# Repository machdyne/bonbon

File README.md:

# Bonbon Computer

Bonbon is a compact FPGA computer designed by Lone Dynamics Corporation.

This repo contains schematics, PCB layouts, pinouts, example firmware, gateware and documentation.

Find more information on the [Bonbon product page](https://machdyne.com/product/bonbon-computer/).

## Blinky 

Building the blinky example requires [Yosys](https://github.com/YosysHQ/yosys), [nextpnr-ice40](https://github.com/YosysHQ/nextpnr) and [IceStorm](https://github.com/YosysHQ/icestorm).

Assuming they are installed, you can simply type `make` to build the gateware, which will be written to output/blinky.bin. You can then connect the Micro-USB port to your computer and use the latest version of [ldprog](https://github.com/machdyne/ldprog) to write the gateware to the device.

## Programming

The RP2040 firmware, FPGA SRAM and flash MMOD can be programmed over the Micro-USB port.

Configure the FPGA SRAM:

```
$ ldprog -b -s blinky.bin
```

Program the flash MMOD:

```
$ ldprog -b -f blinky.bin
```

Note: It should also be possible to program the MMOD over the USB-C port with a USB bootloader but this is not yet officially supported.

## Firmware

Bonbon ships with RP2040 [firmware](firmware) based on the [Müsli](https://github.com/machdyne/musli) firmware which allows it to communicate with [ldprog](https://github.com/machdyne/ldprog).

The firmware is responsible for initializing the system, [configuring and outputting the system clock](https://raspberrypi.github.io/pico-sdk-doxygen/group__hardware__clocks.html#details), and either configuring the FPGA or telling the FPGA to configure itself from the MMOD.

The system clock (CLK\_RP) is 48MHz by default.

The firmware can be updated by holding down the BOOTSEL button, connecting the Micro-USB port to your computer, and then dragging and dropping a new UF2 file to the device filesystem.

## DDMI

See this [SmolDVI fork](https://github.com/machdyne/SmolDVI) for an example of outputting video on the DDMI port.

## Pinouts

 * [MMOD](https://github.com/machdyne/mmod)
 * [DDMI](https://github.com/machdyne/ddmi)

## License

The contents of this repo are released under the [Lone Dynamics Open License](LICENSE.md) with the following exceptions:

- The KiCad design files contain parts of the [kicad-pmod](https://github.com/mithro/kicad-pmod) library which is released under the [Apache License, Version 2.0](https://www.apache.org/licenses/LICENSE-2.0.html).

- The KiCad design files may contain symbols and footprints released under other licenses; please contact us if we've failed to give proper attribution.

Note: You can use these designs for commercial purposes but we ask that instead of producing exact clones, that you either replace our trademarks and logos with your own or add your own next to ours.

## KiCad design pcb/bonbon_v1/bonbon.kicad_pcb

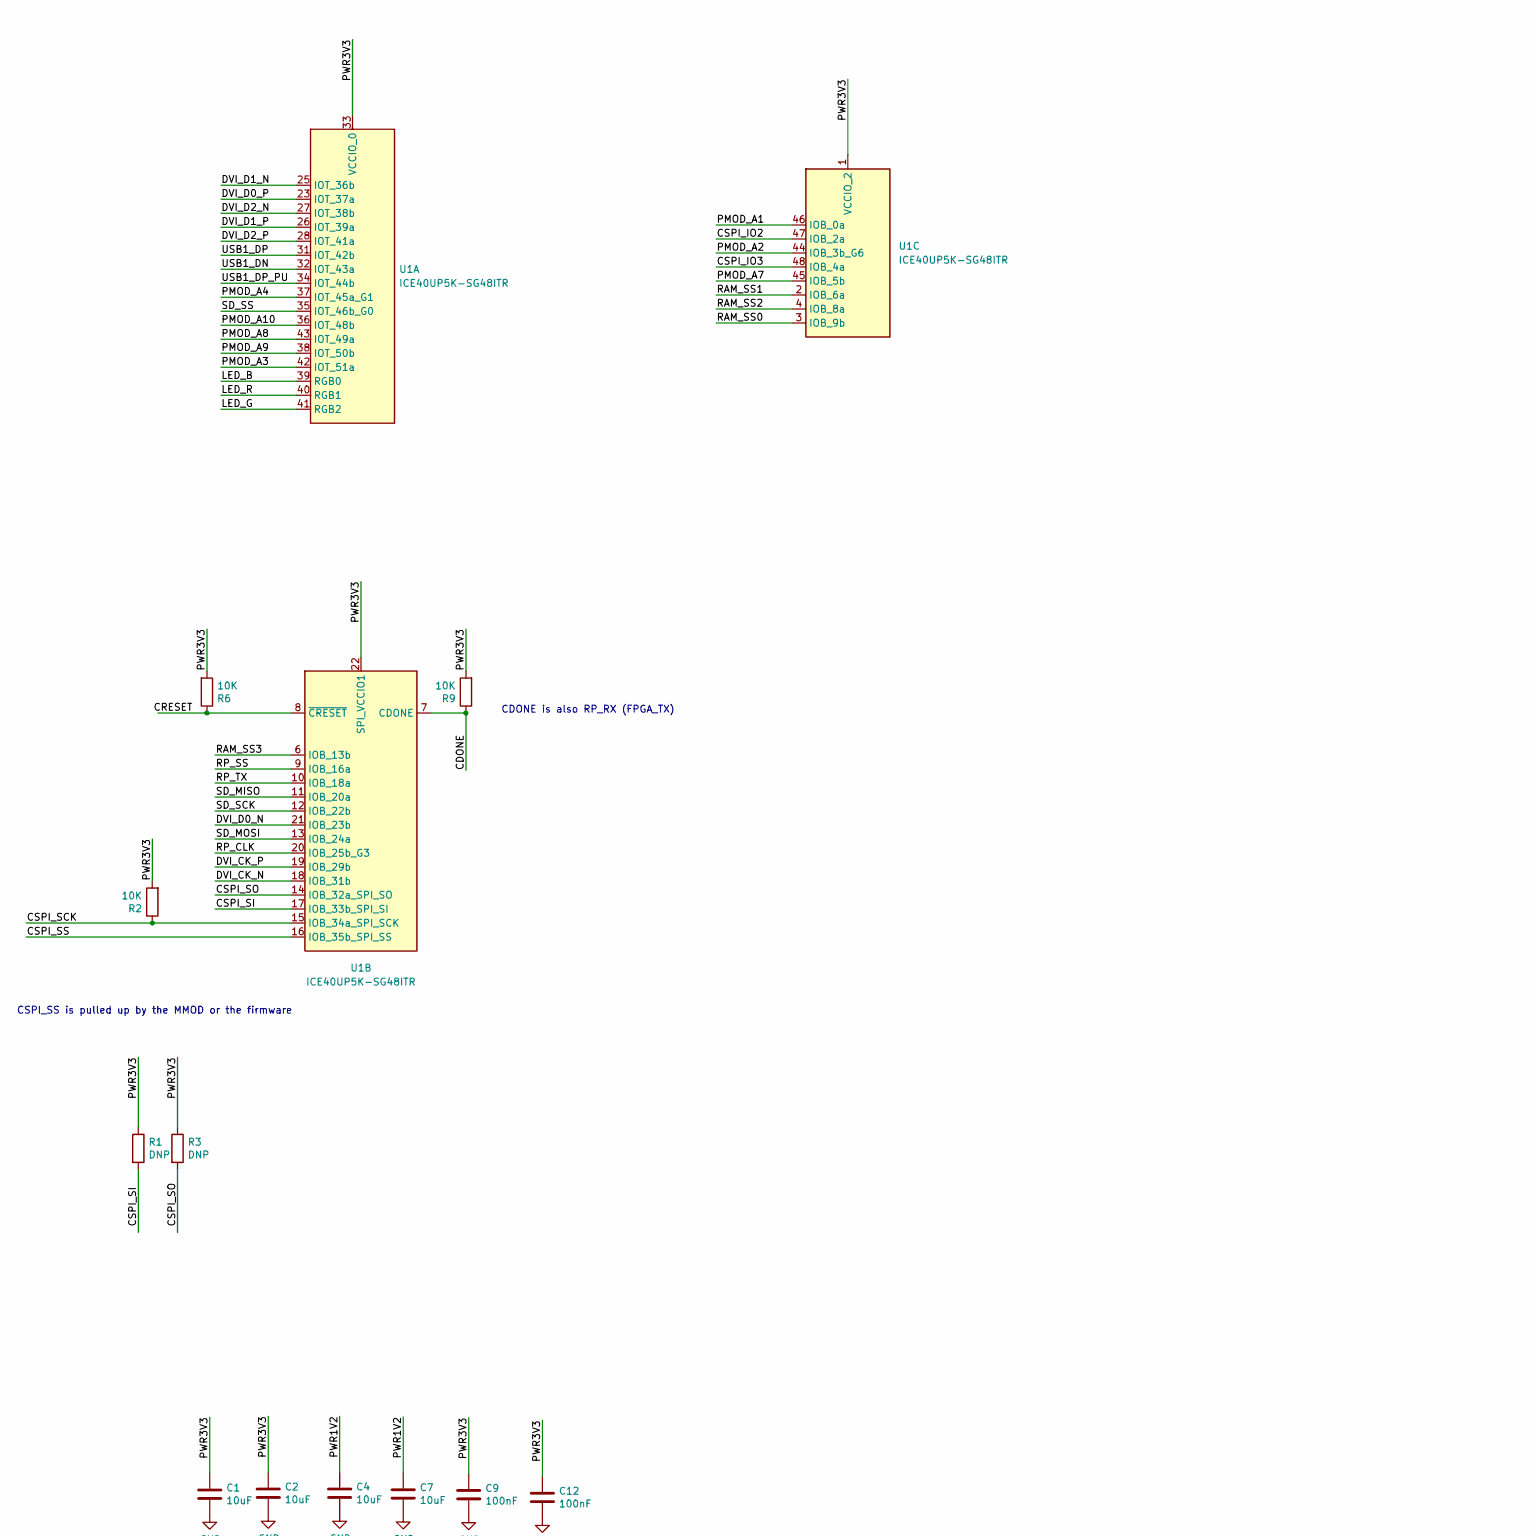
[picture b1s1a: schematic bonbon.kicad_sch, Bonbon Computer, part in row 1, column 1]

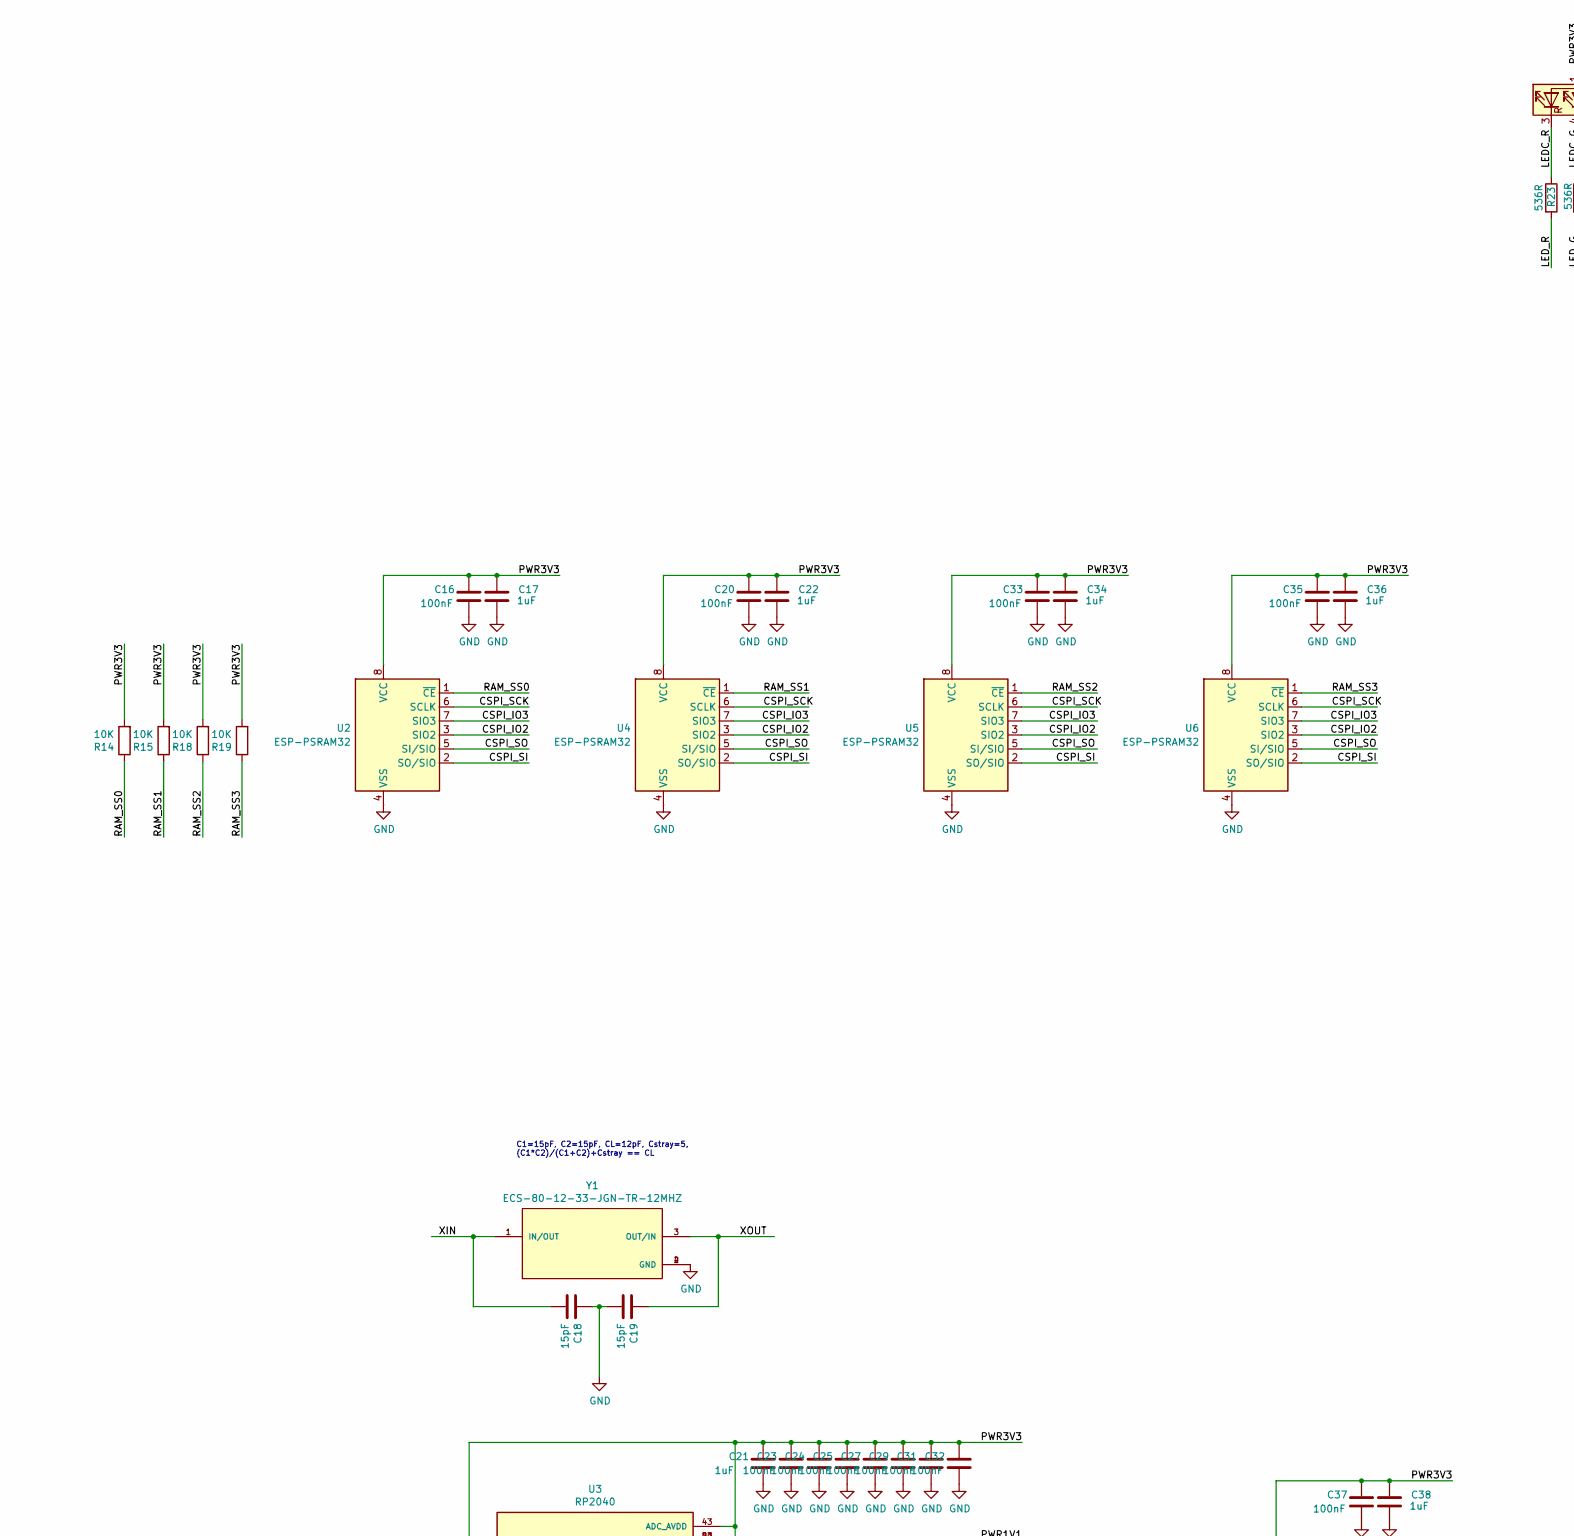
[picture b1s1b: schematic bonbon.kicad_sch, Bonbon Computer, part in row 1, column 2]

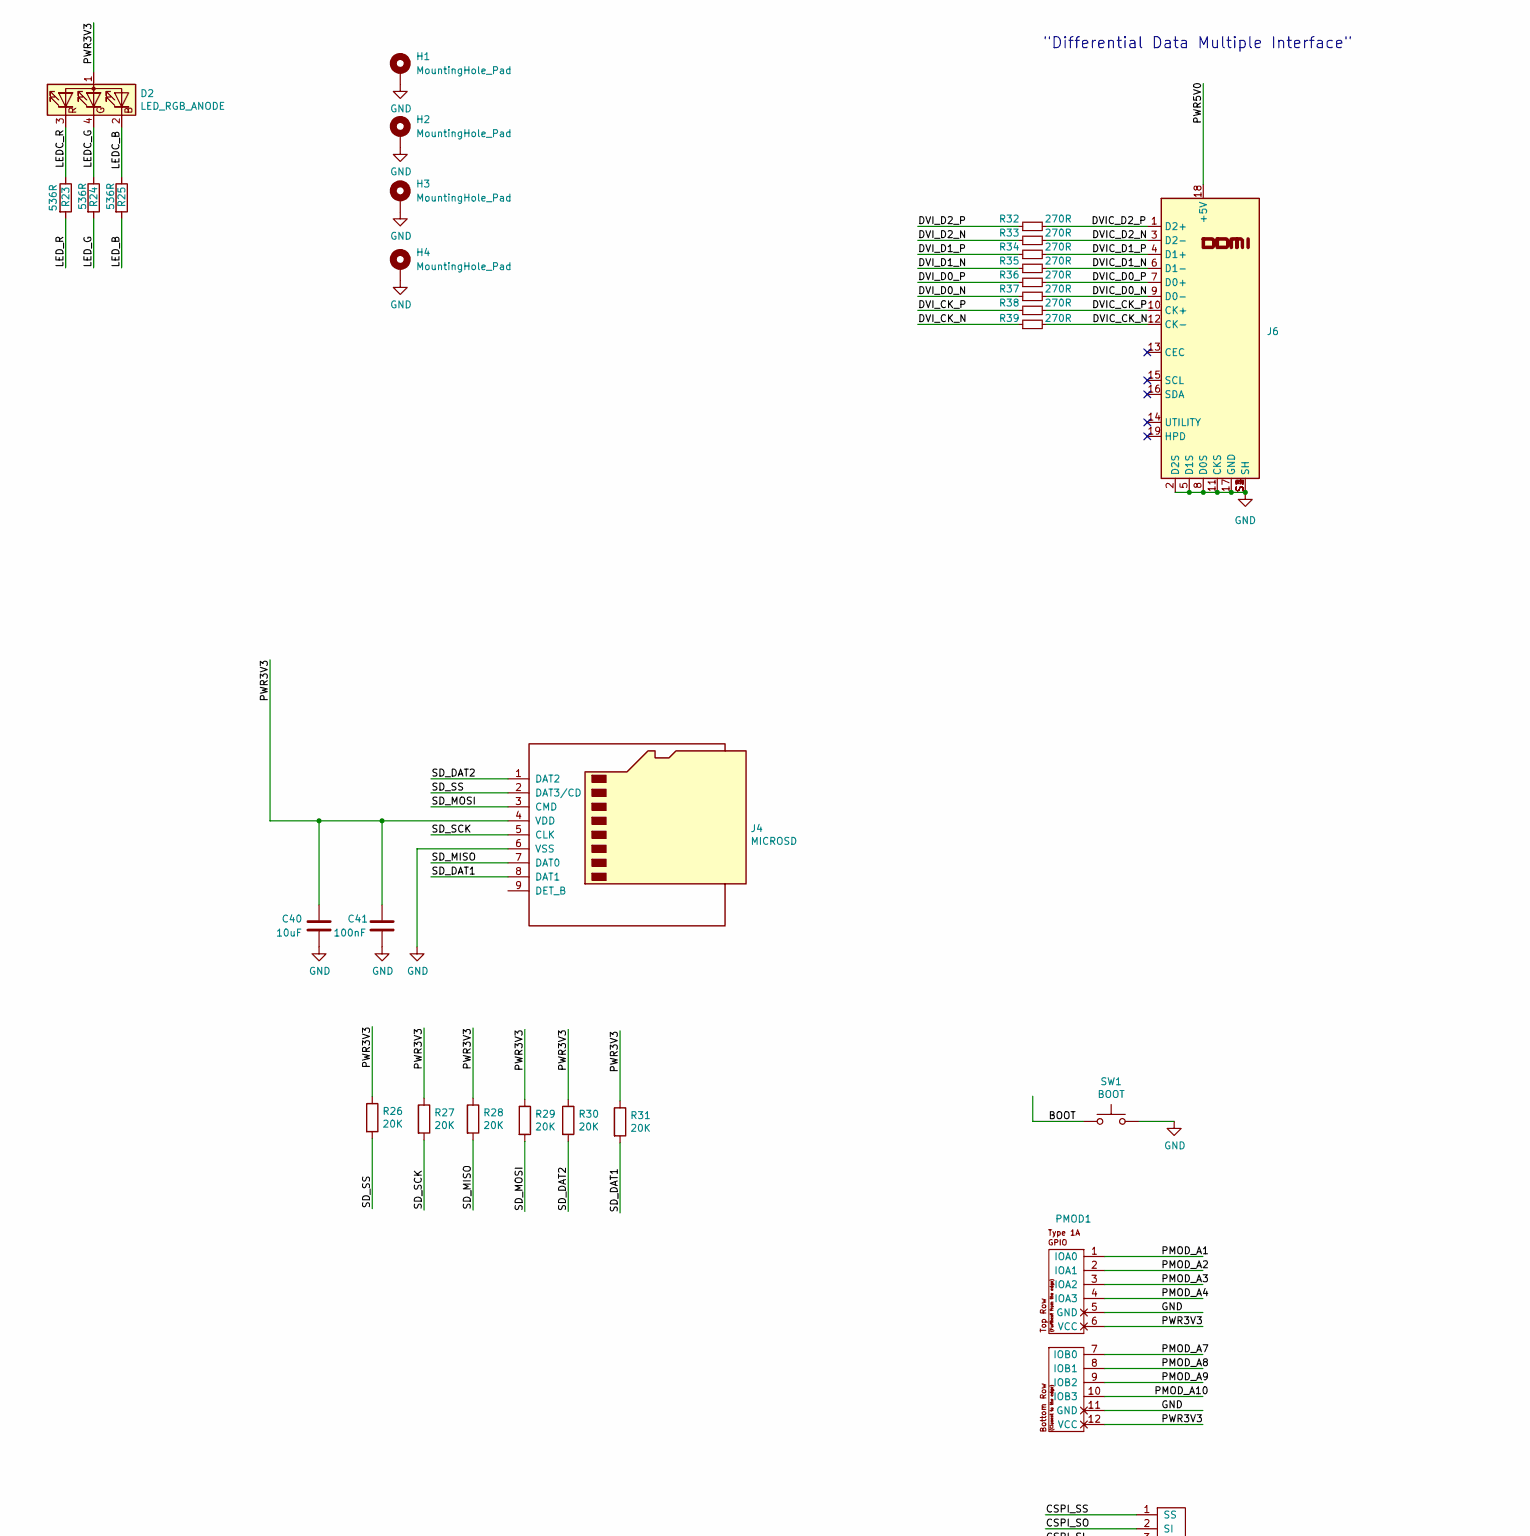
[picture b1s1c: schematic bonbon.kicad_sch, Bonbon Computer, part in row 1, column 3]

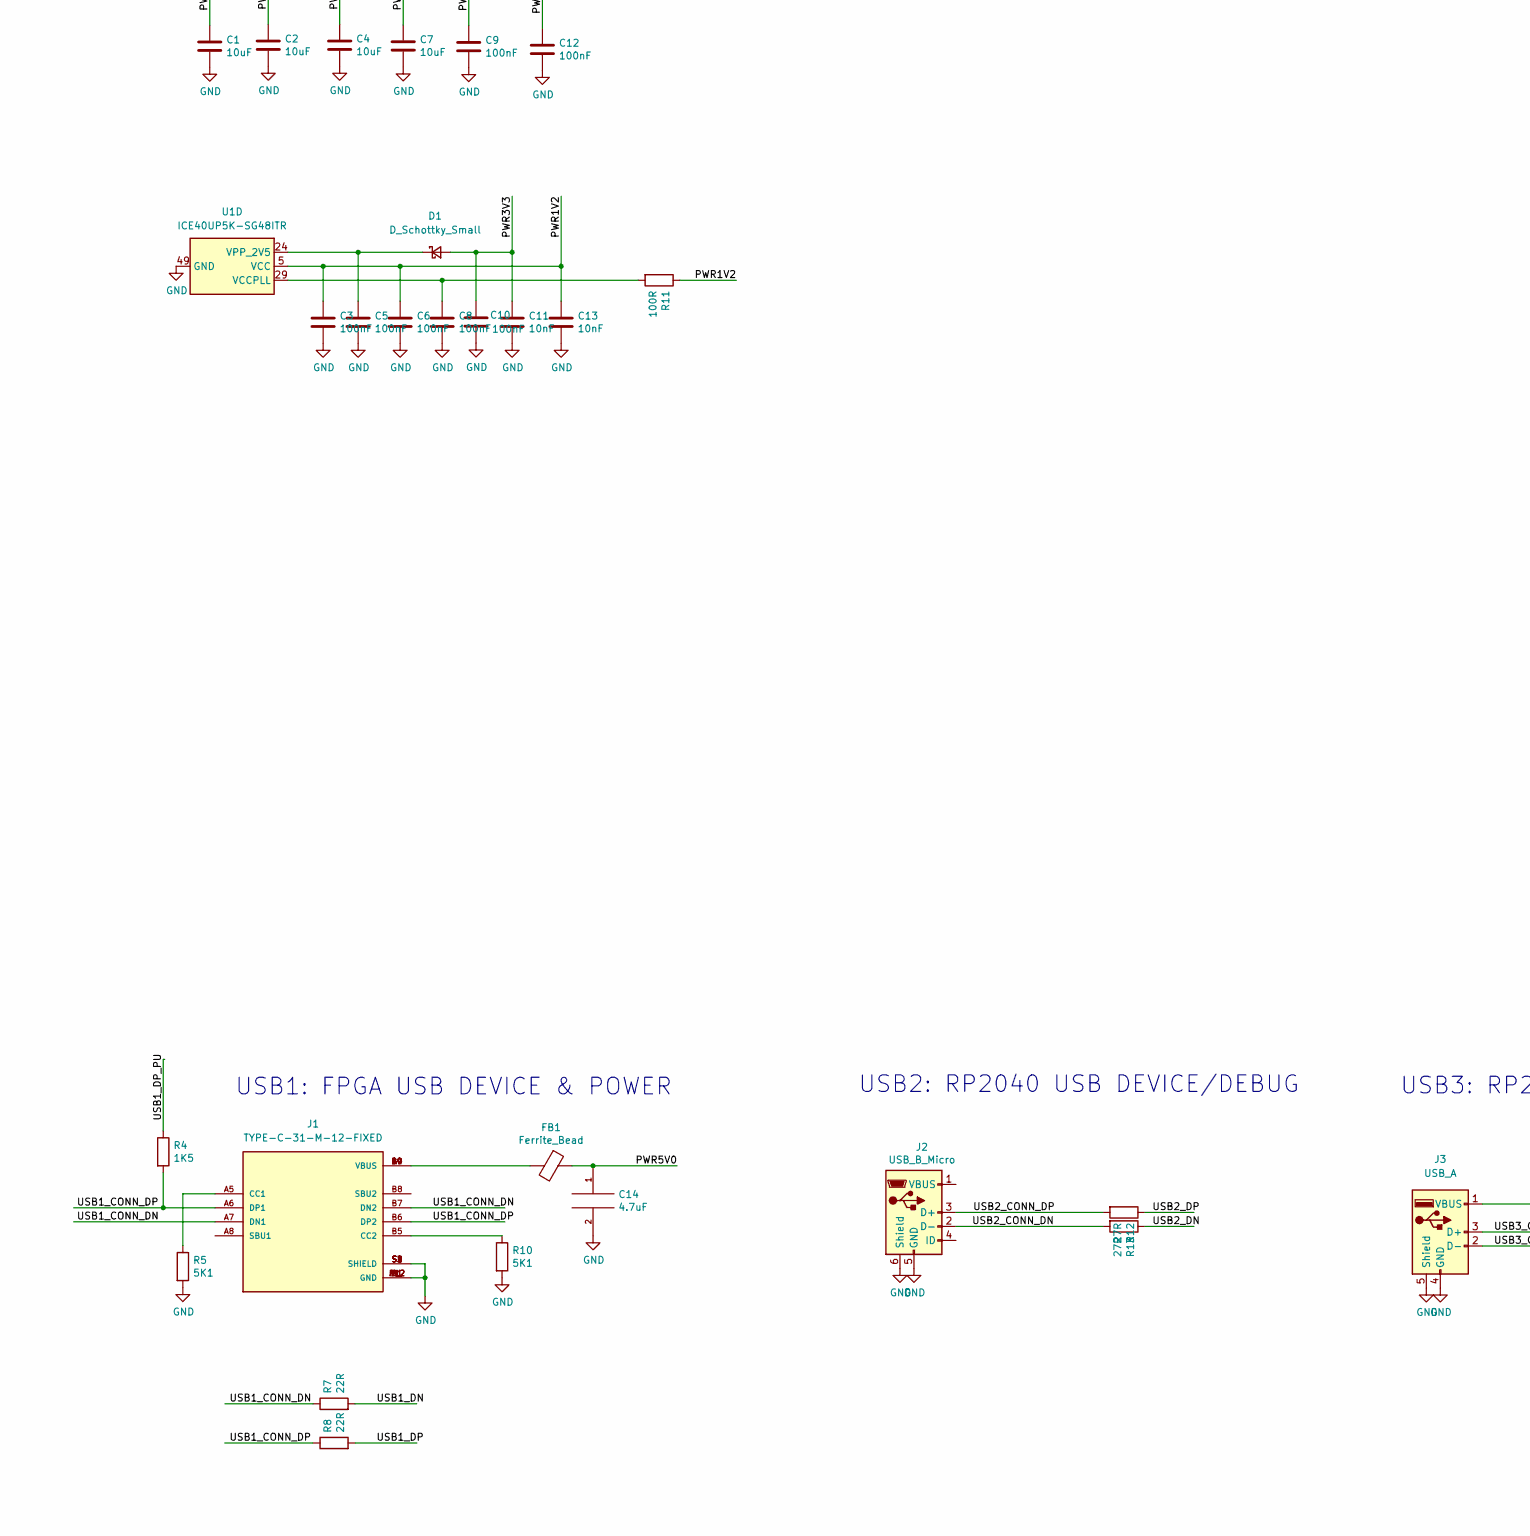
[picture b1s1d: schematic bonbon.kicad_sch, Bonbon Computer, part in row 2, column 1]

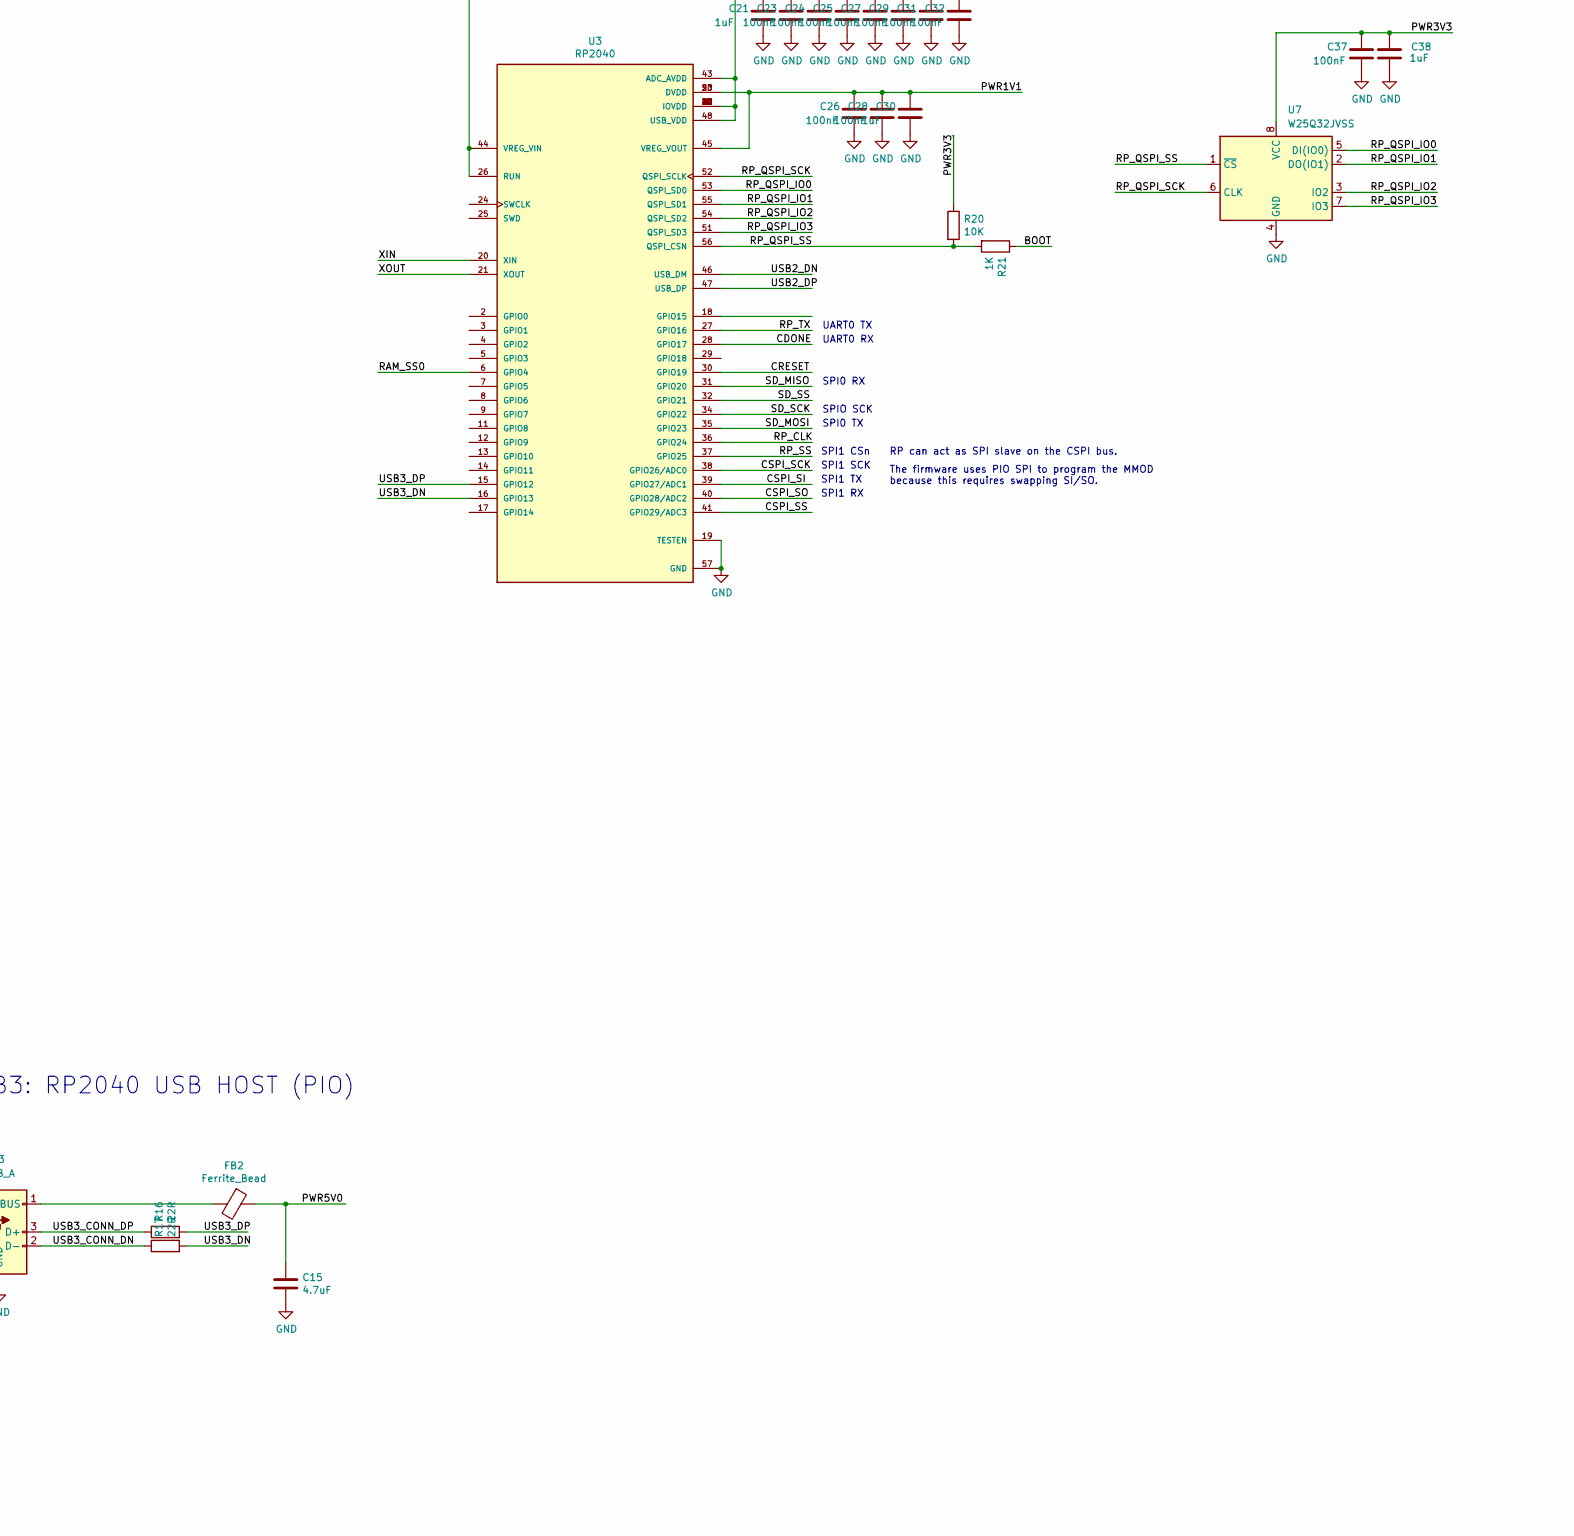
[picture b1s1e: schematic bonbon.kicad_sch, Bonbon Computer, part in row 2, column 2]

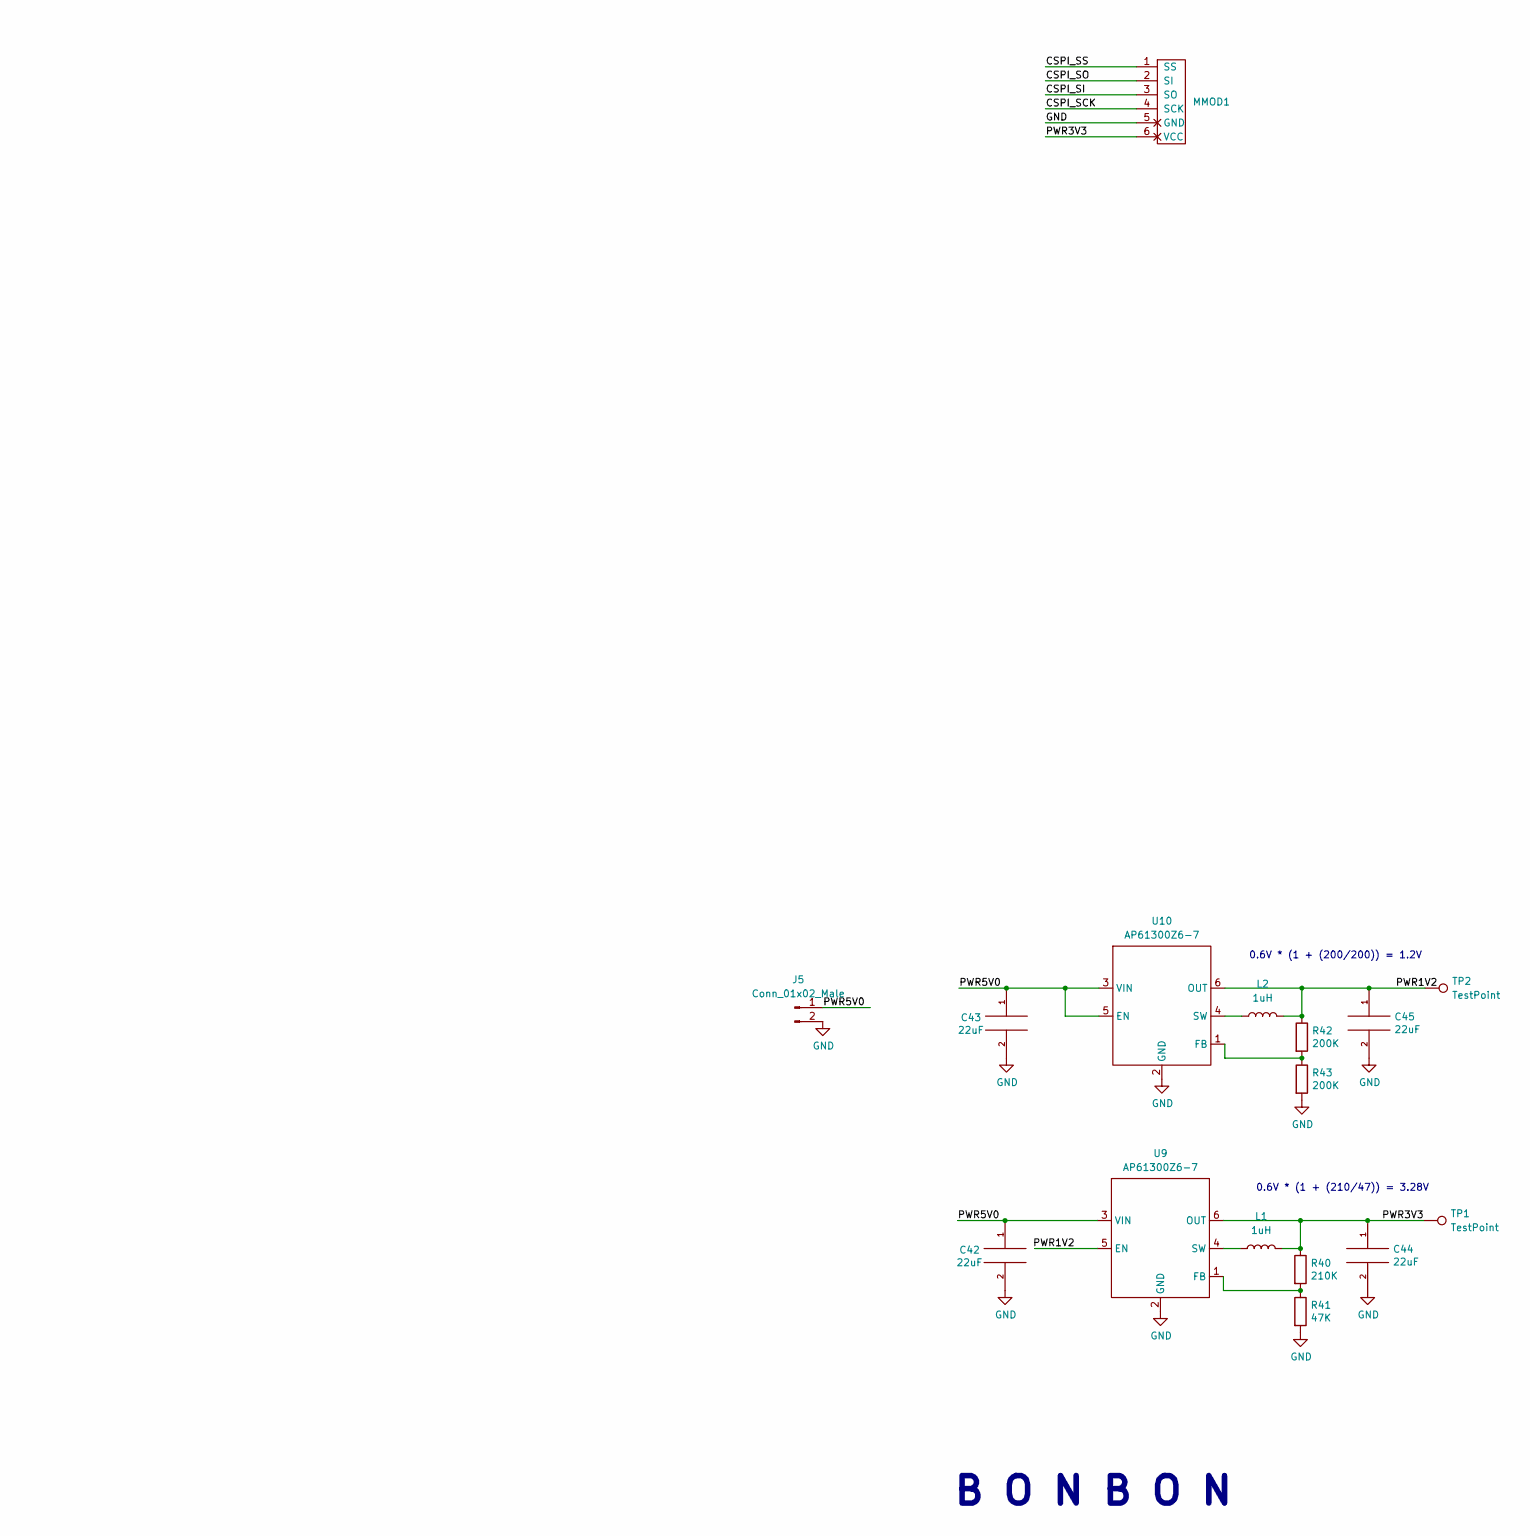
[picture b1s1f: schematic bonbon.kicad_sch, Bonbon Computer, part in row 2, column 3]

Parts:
C1, C2, C4, C7: 10uF; C_0402_1005Metric
C3, C5, C6, C8, C9, C10, C12, C16, C20, C23, C24, C25, C26, C27, C28, C29, C31, C32, C33, C35, C37: 100nF; C_0402_1005Metric
C11, C13: 10nF; C_0402_1005Metric
C14, C15: 4.7uF; R_0603_1608Metric
C17, C21, C22, C30, C34, C36, C38: 1uF; C_0402_1005Metric
C18, C19: 15pF; C_0402_1005Metric
C40: 10uF; R_0402_1005Metric
C41: 100nF; R_0402_1005Metric
C42, C43, C44, C45: 22uF; C_0603_1608Metric
D1: D_Schottky_Small; D_0402_1005Metric
D2: LED_RGB_ANODE; LED_RGB_0606_CHANZON
FB1, FB2: Ferrite_Bead; R_0603_1608Metric
H1, H2, H3, H4: MountingHole_Pad; MountingHole_3.2mm_M3_Pad
J1: TYPE-C-31-M-12-FIXED; USB_C_Receptacle_HRO_TYPE-C-31-M-12-BIG-PADS; PARTREV A
J2: USB_B_Micro; USB_Micro-B_Molex-105017-0001
J3: USB_A; USB_A_Stewart_SS-52100-001_Horizontal
J4: MICROSD; SDCARD
J5: Conn_01x02_Male; PinHeader_1x02_P2.54mm_Vertical
J6: HDMI_TE_1827059-3-FIXED
L1, L2: 1uH; L_0603_1608Metric
MMOD1: MMOD_Host_Socket
PMOD1: PMOD-Device-x2-Type-1A-GPIO; PMOD_2x06_HOST
R1, R3: DNP; R_0402_1005Metric
R2, R6, R9, R14, R15, R18, R19, R20: 10K; R_0402_1005Metric
R4: 1K5; R_0402_1005Metric
R5, R10: 5K1; R_0603_1608Metric
R7, R8, R16, R17: 22R; R_0402_1005Metric
R11: 100R; R_0402_1005Metric
R12, R13: 27R; R_0402_1005Metric
R21: 1K; R_0402_1005Metric
R23, R24, R25: 536R; R_0402_1005Metric
R26, R27, R28, R29, R30, R31: 20K; R_0402_1005Metric
R32, R33, R34, R35, R36, R37, R38, R39: 270R; R_0402_1005Metric
R40: 210K; R_0603_1608Metric
R41: 47K; R_0603_1608Metric
R42, R43: 200K; R_0603_1608Metric
SW1: BOOT; Button_2P_3x4mm
TP1, TP2: TestPoint; TestPoint_THTPad_D1.0mm_Drill0.5mm
U1: ICE40UP5K-SG48ITR; QFN-48-1EP_7x7mm_P0.5mm_EP5.6x5.6mm
U2, U4, U5, U6: ESP-PSRAM32; SOIC-8_3.9x4.9mm_P1.27mm
U3: RP2040; RP2040-QFN-56-OFFICIAL; PARTREV 1.6.1
U7: W25Q32JVSS; SOIC-8_3.9x4.9mm_P1.27mm
U9, U10: AP61300Z6-7; SOT-563
Y1: ECS-80-12-33-JGN-TR-12MHZ; XTAL_ECS-240-8-33-AGN-TR

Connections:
/BOOT: R21.1, SW1.1
/CDONE: R9.1, U1.7 (CDONE), U3.28 (GPIO17)
/CRESET: R6.1, U1.8 (~CRESET), U3.30 (GPIO19)
/CSPI_IO2: U1.47 (IOB_2a), U2.3 (SIO2), U4.3 (SIO2), U5.3 (SIO2), U6.3 (SIO2)
/CSPI_IO3: U1.48 (IOB_4a), U2.7 (SIO3), U4.7 (SIO3), U5.7 (SIO3), U6.7 (SIO3)
/CSPI_SCK: MMOD1.4 (SCK), R2.1, U1.15 (IOB_34a_SPI_SCK), U2.6 (SCLK), U3.38 (GPIO26/ADC0), U4.6 (SCLK), U5.6 (SCLK), U6.6 (SCLK)
/CSPI_SI: MMOD1.3 (SO), R1.2, U1.17 (IOB_33b_SPI_SI), U2.2 (SO/SIO), U3.39 (GPIO27/ADC1), U4.2 (SO/SIO), U5.2 (SO/SIO), U6.2 (SO/SIO)
/CSPI_SO: MMOD1.2 (SI), R3.2, U1.14 (IOB_32a_SPI_SO), U2.5 (SI/SIO), U3.40 (GPIO28/ADC2), U4.5 (SI/SIO), U5.5 (SI/SIO), U6.5 (SI/SIO)
/CSPI_SS: MMOD1.1 (SS), U1.16 (IOB_35b_SPI_SS), U3.41 (GPIO29/ADC3)
/DVIC_CK_N: J6.12 (CK-), R39.2
/DVIC_CK_P: J6.10 (CK+), R38.2
/DVIC_D0_N: J6.9 (D0-), R37.2
/DVIC_D0_P: J6.7 (D0+), R36.2
/DVIC_D1_N: J6.6 (D1-), R35.2
/DVIC_D1_P: J6.4 (D1+), R34.2
/DVIC_D2_N: J6.3 (D2-), R33.2
/DVIC_D2_P: J6.1 (D2+), R32.2
/DVI_CK_N: R39.1, U1.18 (IOB_31b)
/DVI_CK_P: R38.1, U1.19 (IOB_29b)
/DVI_D0_N: R37.1, U1.21 (IOB_23b)
/DVI_D0_P: R36.1, U1.23 (IOT_37a)
/DVI_D1_N: R35.1, U1.25 (IOT_36b)
/DVI_D1_P: R34.1, U1.26 (IOT_39a)
/DVI_D2_N: R33.1, U1.27 (IOT_38b)
/DVI_D2_P: R32.1, U1.28 (IOT_41a)
/LEDC_B: D2.2 (BK), R25.1
/LEDC_G: D2.4 (GK), R24.1
/LEDC_R: D2.3 (RK), R23.1
/LED_B: R25.2, U1.39 (RGB0)
/LED_G: R24.2, U1.41 (RGB2)
/LED_R: R23.2, U1.40 (RGB1)
/PMOD_A1: PMOD1.1 (IOA0), U1.46 (IOB_0a)
/PMOD_A2: PMOD1.2 (IOA1), U1.44 (IOB_3b_G6)
/PMOD_A3: PMOD1.3 (IOA2), U1.42 (IOT_51a)
/PMOD_A4: PMOD1.4 (IOA3), U1.37 (IOT_45a_G1)
/PMOD_A7: PMOD1.7 (IOB0), U1.45 (IOB_5b)
/PMOD_A8: PMOD1.8 (IOB1), U1.43 (IOT_49a)
/PMOD_A9: PMOD1.9 (IOB2), U1.38 (IOT_50b)
/PMOD_A10: PMOD1.10 (IOB3), U1.36 (IOT_48b)
/PWR1V1: C26.1, C28.1, C30.1, U3.23 (DVDD), U3.45 (VREG_VOUT), U3.50 (DVDD)
/PWR1V2: C3.1, C4.1, C6.1, C7.1, C13.1, C45.1, L2.2, R11.1, R42.1, TP2.1, U1.5 (VCC), U1.30 (VCC), U9.5 (EN), U10.6 (OUT)
/PWR3V3: C1.1, C2.1, C9.1, C10.1, C11.1, C12.1, C16.1, C17.1, C20.1, C21.1, C22.1, C23.1, C24.1, C25.1, C27.1, C29.1, C31.1, C32.1, C33.1, C34.1, C35.1, C36.1, C37.1, C38.1, C40.1, C41.1, C44.1, D1.2 (A), D2.1 (A), J4.4 (VDD), L1.2, MMOD1.6 (VCC), PMOD1.6 (VCC), PMOD1.12 (VCC), R1.1, R2.2, R3.1, R6.2, R9.2, R14.2, R15.2, R18.2, R19.2, R20.1, R26.1, R27.1, R28.1, R29.1, R30.1, R31.1, R40.1, TP1.1, U1.1 (VCCIO_2), U1.22 (SPI_VCCIO1), U1.33 (VCCIO_0), U2.8 (VCC), U3.1 (IOVDD), U3.10 (IOVDD), U3.22 (IOVDD), U3.26 (RUN), U3.33 (IOVDD), U3.42 (IOVDD), U3.43 (ADC_AVDD), U3.44 (VREG_VIN), U3.48 (USB_VDD), U3.49 (IOVDD), U4.8 (VCC), U5.8 (VCC), U6.8 (VCC), U7.8 (VCC), U9.6 (OUT)
/PWR5V0: C14.1, C15.1, C42.1, C43.1, FB1.1, FB2.1, J5.1, J6.18 (+5V), U9.3 (VIN), U10.3 (VIN), U10.5 (EN)
/RAM_SS0: R14.1, U1.3 (IOB_9b), U2.1 (~CE), U3.6 (GPIO4)
/RAM_SS1: R15.1, U1.2 (IOB_6a), U4.1 (~CE)
/RAM_SS2: R18.1, U1.4 (IOB_8a), U5.1 (~CE)
/RAM_SS3: R19.1, U1.6 (IOB_13b), U6.1 (~CE)
/RP_CLK: U1.20 (IOB_25b_G3), U3.36 (GPIO24)
/RP_QSPI_IO0: U3.53 (QSPI_SD0), U7.5 (DI(IO0))
/RP_QSPI_IO1: U3.55 (QSPI_SD1), U7.2 (DO(IO1))
/RP_QSPI_IO2: U3.54 (QSPI_SD2), U7.3 (IO2)
/RP_QSPI_IO3: U3.51 (QSPI_SD3), U7.7 (IO3)
/RP_QSPI_SCK: U3.52 (QSPI_SCLK), U7.6 (CLK)
/RP_QSPI_SS: R20.2, R21.2, U3.56 (QSPI_CSN), U7.1 (~CS)
/RP_SS: U1.9 (IOB_16a), U3.37 (GPIO25)
/RP_TX: U1.10 (IOB_18a), U3.27 (GPIO16)
/SD_DAT1: J4.8 (DAT1), R31.2
/SD_DAT2: J4.1 (DAT2), R30.2
/SD_MISO: J4.7 (DAT0), R28.2, U1.11 (IOB_20a), U3.31 (GPIO20)
/SD_MOSI: J4.3 (CMD), R29.2, U1.13 (IOB_24a), U3.35 (GPIO23)
/SD_SCK: J4.5 (CLK), R27.2, U1.12 (IOB_22b), U3.34 (GPIO22)
/SD_SS: J4.2 (DAT3/CD), R26.2, U1.35 (IOT_46b_G0), U3.32 (GPIO21)
/USB1_CONN_DN: J1.A7 (DN1), J1.B7 (DN2), R7.1
/USB1_CONN_DP: J1.A6 (DP1), J1.B6 (DP2), R4.2, R8.1
/USB1_DN: R7.2, U1.32 (IOT_43a)
/USB1_DP: R8.2, U1.31 (IOT_42b)
/USB1_DP_PU: R4.1, U1.34 (IOT_44b)
/USB2_CONN_DN: J2.2 (D-), R13.2
/USB2_CONN_DP: J2.3 (D+), R12.2
/USB2_DN: R13.1, U3.46 (USB_DM)
/USB2_DP: R12.1, U3.47 (USB_DP)
/USB3_CONN_DN: J3.2 (D-), R17.1
/USB3_CONN_DP: J3.3 (D+), R16.1
/USB3_DN: R17.2, U3.16 (GPIO13)
/USB3_DP: R16.2, U3.15 (GPIO12)
/XIN: C18.2, U3.20 (XIN), Y1.1 (IN/OUT)
/XOUT: C19.1, U3.21 (XOUT), Y1.3 (OUT/IN)
GND: C1.2, C2.2, C3.2, C4.2, C5.2, C6.2, C7.2, C8.2, C9.2, C10.2, C11.2, C12.2, C13.2, C14.2, C15.2, C16.2, C17.2, C18.1, C19.2, C20.2, C21.2, C22.2, C23.2, C24.2, C25.2, C26.2, C27.2, C28.2, C29.2, C30.2, C31.2, C32.2, C33.2, C34.2, C35.2, C36.2, C37.2, C38.2, C40.2, C41.2, C42.2, C43.2, C44.2, C45.2, H1.1, H2.1, H3.1, H4.1, J1.A1 (GND), J1.A12 (GND), J1.B1 (GND), J1.B12 (GND), J1.S1 (SHIELD), J1.S2 (SHIELD), J1.S3 (SHIELD), J1.S4 (SHIELD), J2.5 (GND), J2.6 (Shield), J3.4 (GND), J3.5 (Shield), J4.6 (VSS), J5.2, J6.2 (D2S), J6.5 (D1S), J6.8 (D0S), J6.11 (CKS), J6.17 (GND), J6.S1 (SH), J6.S2 (SH), J6.S3 (SH), J6.S4 (SH), MMOD1.5 (GND), PMOD1.5 (GND), PMOD1.11 (GND), R5.2, R10.2, R41.2, R43.2, SW1.2, U1.49 (GND), U2.4 (VSS), U3.19 (TESTEN), U3.57 (GND), U4.4 (VSS), U5.4 (VSS), U6.4 (VSS), U7.4 (GND), U9.2 (GND), U10.2 (GND), Y1.2 (GND), Y1.4 (GND)
unnamed: C5.1, D1.1 (K), U1.24 (VPP_2V5)
unnamed: C8.1, R11.2, U1.29 (VCCPLL)
unnamed: FB1.2, J1.A4 (VBUS), J1.A9 (VBUS), J1.B4 (VBUS), J1.B9 (VBUS)
unnamed: FB2.2, J3.1 (VBUS)
unnamed: J1.A5 (CC1), R5.1
unnamed: J1.B5 (CC2), R10.1
unnamed: L1.1, U9.4 (SW)
unnamed: L2.1, U10.4 (SW)
unnamed: R40.2, R41.1, U9.1 (FB)
unnamed: R42.2, R43.1, U10.1 (FB)

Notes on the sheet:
CDONE is also RP_RX (FPGA_TX)
UART0 RX
SPI1 TX
USB3: RP2040 USB HOST (PIO)
CSPI_SS is pulled up by the MMOD or the firmware
0.6V * (1 + (210/47)) = 3.28V
SPI1 CSn
C1=15pF, C2=15pF, CL=12pF, Cstray=5, (C1*C2)/(C1+C2)+Cstray == CL
SPI1 RX
SPI1 SCK
UART0 TX
0.6V * (1 + (200/200)) = 1.2V
RP can act as SPI slave on the CSPI bus.
SPI0 TX
USB1: FPGA USB DEVICE & POWER
"Differential Data Multiple Interface"
SPIO SCK
USB2: RP2040 USB DEVICE/DEBUG
The firmware uses PIO SPI to program the MMOD because this requires swapping SI/SO.
SPI0 RX
B O N B O N

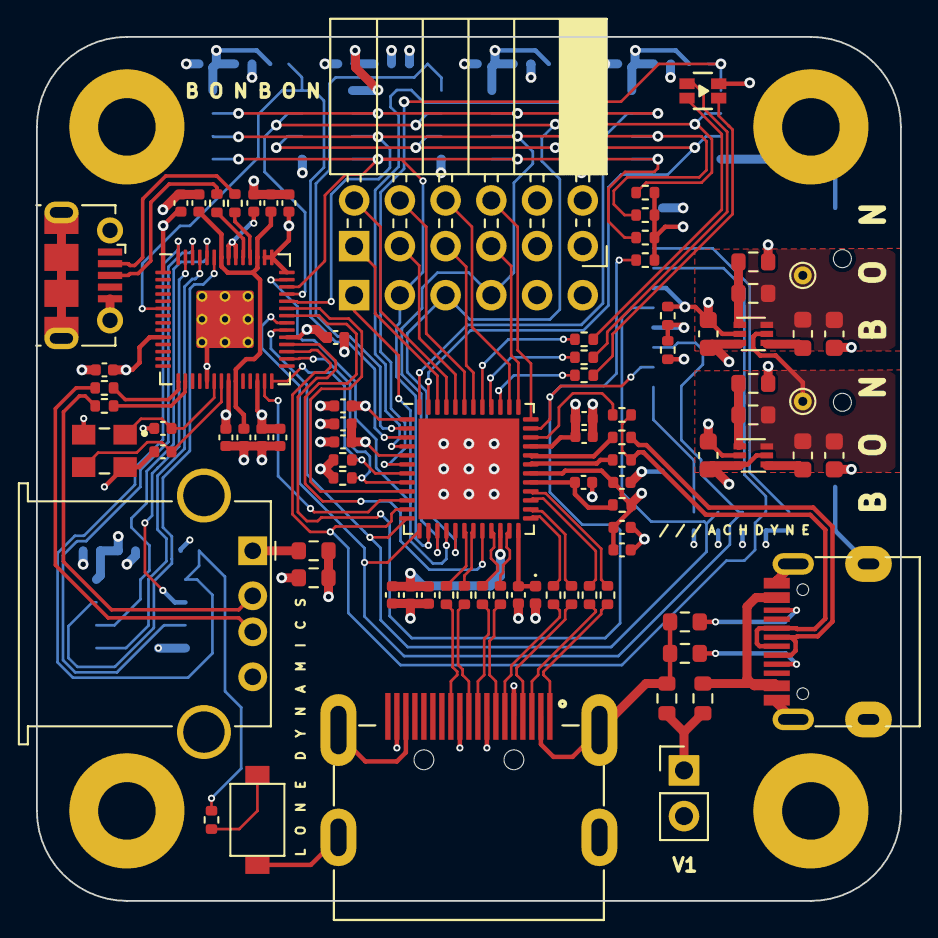
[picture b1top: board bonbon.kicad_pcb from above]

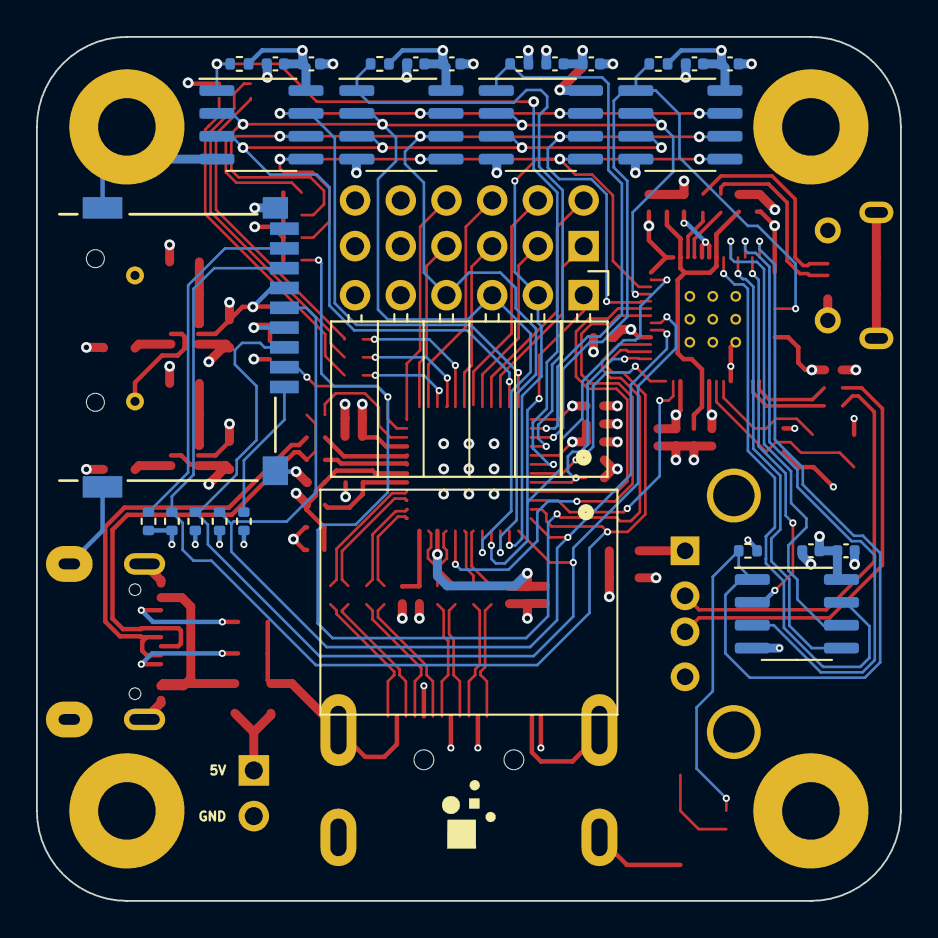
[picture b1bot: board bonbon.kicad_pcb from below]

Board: 4 copper layers, 48.0 x 48.0 mm, 117 parts (27 on the bottom side), 88 nets.

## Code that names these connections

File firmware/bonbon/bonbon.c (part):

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#define ICE40_CDONE 17
#define ICE40_CRESET 19

#define RAM_SS0 4
#define SD_SS 15

#define SPI_MODE_HW 1
#define SPI_MODE_PIO 2
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	gpio_init(MUSLI_SPI_SCK_PIN);
	gpio_disable_pulls(MUSLI_SPI_SCK_PIN);

	gpio_init(RAM_SS0);
	gpio_disable_pulls(RAM_SS0);

	gpio_init(SD_SS);
	gpio_disable_pulls(SD_SS);

	gpio_init(ICE40_CDONE);
	gpio_disable_pulls(ICE40_CDONE);
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			usb_started = 1;
		}

		int cdone = gpio_get(ICE40_CDONE);
		if (cdone && cdone != kfc_prev && !bonbon_fpga_configured) {
			init_bonbon_postconf();
		}
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
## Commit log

2022-08-23 add schematics
2023-01-25 change rp_clk to 48mhz
2023-02-01 fix wrong gpio for cdone
2023-02-02 update image with 48mhz clock output, fixed cdone
2023-02-04 update firmware
2023-05-22 add pcb

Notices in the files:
firmware/bonbon/bonbon.c:
Copyright (c) 2020 Raspberry Pi (Trading) Ltd.
Copyright (c) 2022 Lone Dynamics Corporation <info@lonedynamics.com>
SPDX-License-Identifier: BSD-3-Clause
pcb/bonbon_v1/bonbon.kicad_sch:
Copyright © 2022 Lone Dynamics Corporation
